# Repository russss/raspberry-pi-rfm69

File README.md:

# Raspberry Pi RFM69 Interface

This is a Raspberry Pi interface to the HopeRF RFM69 module, designed
for the [UKHASnet](https://ukhas.net) project.

It supports up to 4 channels with independent RFM69 transceivers, intended
for experimenting with sectored antennas and long-range backhaul links,
but can also be used with just a single RFM69 for more normal applications.

For code which works with this, check out my [rfm69
python library](https://github.com/russss/rfm69-python).

## BOM

To use just a single RFM69 channel, you will need:

* IC1: RFM69[H][W]
* J1: 40-pin socket (e.g. Farnell 7992033)
* P1: Edge-launch SMA socket

To use more than one RFM69, you'll additionally need:

* IC5: 3.3V 800mA regulator in SOT-223 package e.g. NCP1117 (Farnell 1652366)
* C1, C2: 10uF 0805 SMD capacitors
* IC6: 74HC139 Demultiplexer, TSSOP-16 (Farnell 2444981)
* Plus additional RFM69s and SMA sockets

To use one-wire sensors if you require a strong pull-up:

* R1: A 4k7 0805 SMD resistor

## Assembly

If you want to use a single RFM69, you'll need to bridge jumpers J1 and
J2. J1 connects the 3v3 bus to the RPi's (which will *just about* run
one RFM69 from my experience).

J2 bypasses the demultiplexer on the SPI chip select line and
connects it directly to the first RFM69.

## Pin Mappings

|Module | Interrupt (DIO0) | Reset  |
|-------|------------------|--------|
|1      | GPIO20           | GPIO21 |
|2      | GPIO02           | GPIO03 |
|3      | GPIO27           | GPIO22 |
|4      | GPIO19           | GPIO26 |

* 1-wire: GPIO4
* NSS Select: GPIO23 (bit 1), GPIO24 (bit 2)

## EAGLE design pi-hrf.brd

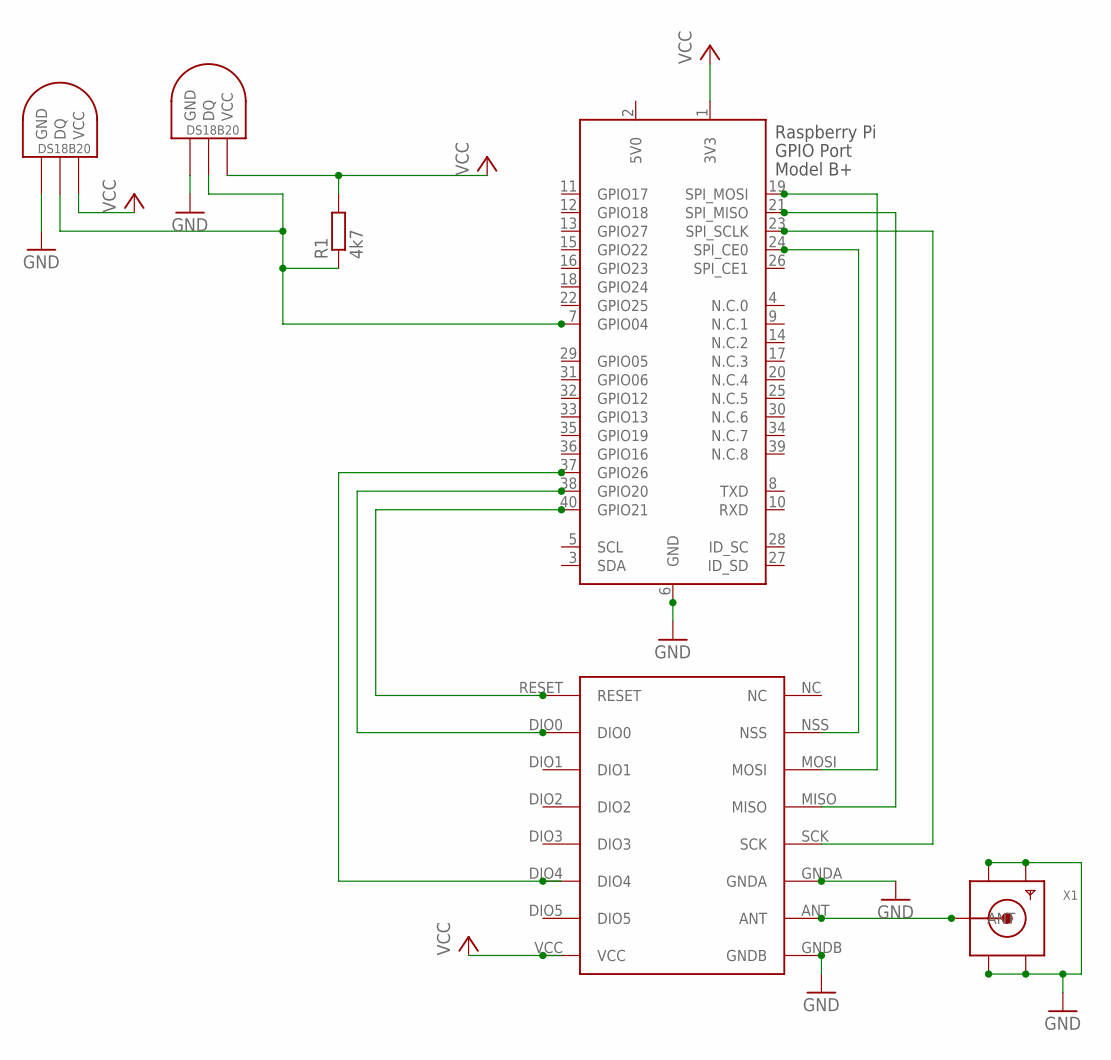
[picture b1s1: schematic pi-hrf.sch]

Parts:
R1: 4k7; 0207/10
U1: RFM69HW; RFM
U$2, U$3: DS1820TO92; DS1820
X1: SMA_EDGELAUNCH
X2: RASPI_BOARD_B+_E3P; RASPI_BOARD_B+_EDGES_3DRILL_PAD

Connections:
5V0: X2.2 (5V0)
GND: U1.GNDA, U1.GNDB, U$2.GND, U$3.GND, X1.GND@1 (GND4), X1.GND@2 (GND3), X1.GND@3 (GND2), X1.GND@4 (GND1), X2.6 (GND)
unnamed: U1.NSS, X2.24 (SPI_CE0)
unnamed: U1.SCK, X2.23 (SPI_SCLK)
unnamed: U1.MOSI, X2.19 (SPI_MOSI)
unnamed: R1.1, U$2.DQ, U$3.DQ, X2.7 (GPIO04)
unnamed: U1.ANT, X1.P (ANT)
unnamed: U1.RESET, X2.40 (GPIO21)
unnamed: U1.DIO0, X2.38 (GPIO20)
unnamed: U1.DIO4, X2.37 (GPIO26)
unnamed: U1.MISO, X2.21 (SPI_MISO)
VCC: R1.2, U1.VCC, U$2.VDD (VCC), U$3.VDD (VCC), X2.1 (3V3)

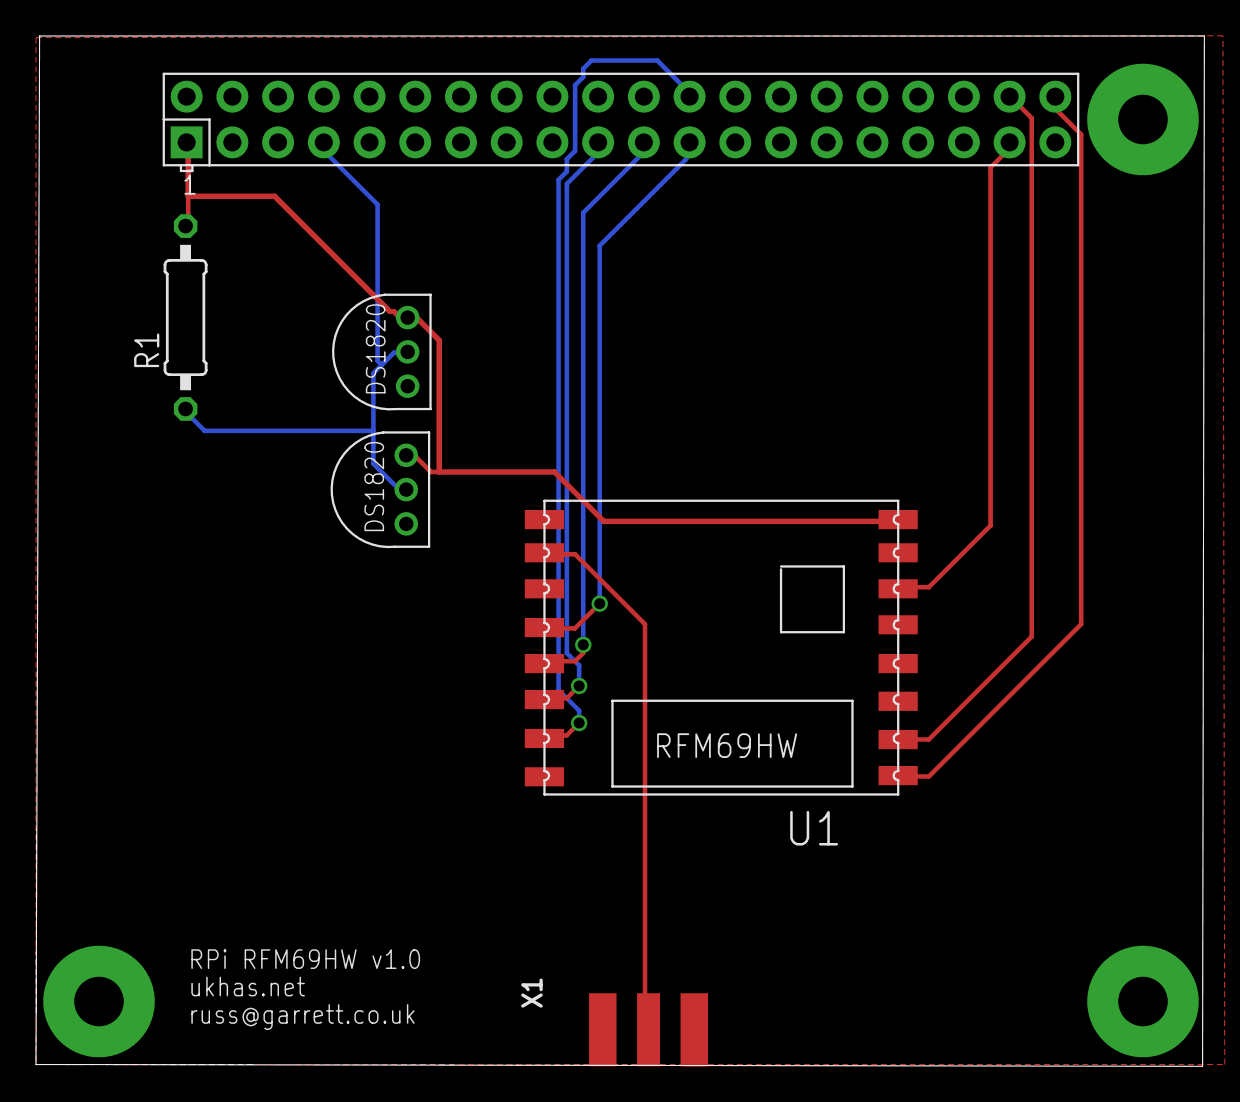
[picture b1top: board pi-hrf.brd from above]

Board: 2 copper layers, 64.9 x 57.2 mm, 6 parts (0 on the bottom side), 11 nets.

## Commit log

2016-09-12 Version 2
2016-09-12 Readme update
2016-09-12 Add CERN OHL
2016-09-12 Readme tweak
2016-09-13 Version 2.0
